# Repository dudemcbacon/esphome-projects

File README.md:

# esphome-projects
my little projects

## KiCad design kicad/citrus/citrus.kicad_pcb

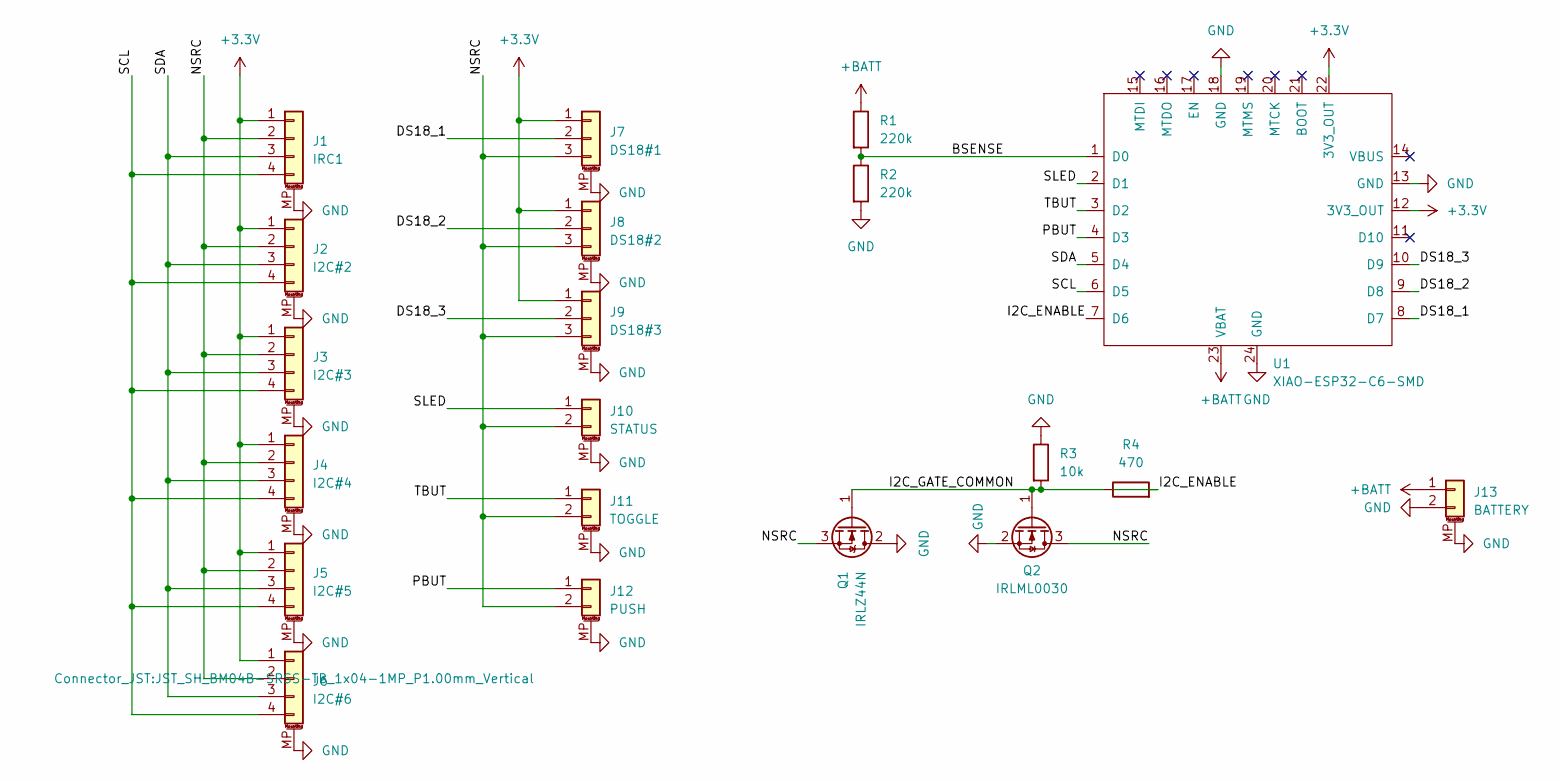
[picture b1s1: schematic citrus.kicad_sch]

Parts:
J1: IRC1; JST_SH_BM04B-SRSS-TB_1x04-1MP_P1.00mm_Vertical
J2: I2C#2; JST_SH_BM04B-SRSS-TB_1x04-1MP_P1.00mm_Vertical
J3: I2C#3; JST_SH_BM04B-SRSS-TB_1x04-1MP_P1.00mm_Vertical
J4: I2C#4; JST_SH_BM04B-SRSS-TB_1x04-1MP_P1.00mm_Vertical
J5: I2C#5; JST_SH_BM04B-SRSS-TB_1x04-1MP_P1.00mm_Vertical
J6: I2C#6; JST_SH_BM04B-SRSS-TB_1x04-1MP_P1.00mm_Vertical
J7: DS18#1; JST_SH_BM03B-SRSS-TB_1x03-1MP_P1.00mm_Vertical
J8: DS18#2; JST_SH_BM03B-SRSS-TB_1x03-1MP_P1.00mm_Vertical
J9: DS18#3; JST_SH_BM03B-SRSS-TB_1x03-1MP_P1.00mm_Vertical
J10: STATUS; JST_SH_BM02B-SRSS-TB_1x02-1MP_P1.00mm_Vertical
J11: TOGGLE; JST_SH_BM02B-SRSS-TB_1x02-1MP_P1.00mm_Vertical
J12: PUSH; JST_SH_BM02B-SRSS-TB_1x02-1MP_P1.00mm_Vertical
J13: BATTERY; JST_SH_BM02B-SRSS-TB_1x02-1MP_P1.00mm_Vertical
Q1: IRLZ44N; TO-220-3_Vertical
Q2: IRLML0030; SOT-23
R1, R2: 220k; R_Axial_DIN0207_L6.3mm_D2.5mm_P7.62mm_Horizontal
R3: 10k; R_Axial_DIN0207_L6.3mm_D2.5mm_P7.62mm_Horizontal
R4: 470; R_Axial_DIN0207_L6.3mm_D2.5mm_P7.62mm_Horizontal
U1: XIAO-ESP32-C6-SMD

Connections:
+3.3V: J1.1, J2.1, J3.1, J4.1, J5.1, J6.1, J7.1, J8.1, J9.1, U1.12 (3V3_OUT), U1.22 (3V3_OUT)
+BATT: J13.1, R1.1, U1.23 (VBAT)
/BSENSE: R1.2, R2.1, U1.1 (D0)
/DS18_1: J7.2, U1.8 (D7)
/DS18_2: J8.2, U1.9 (D8)
/DS18_3: J9.2, U1.10 (D9)
/I2C_ENABLE: R4.2, U1.7 (D6)
/I2C_GATE_COMMON: Q1.1 (G), Q2.1 (G), R3.2, R4.1
/NSRC: J1.2, J2.2, J3.2, J4.2, J5.2, J6.2, J7.3, J8.3, J9.3, J10.2, J11.2, J12.2, Q1.3 (S), Q2.3 (D)
/PBUT: J12.1, U1.4 (D3)
/SCL: J1.4, J2.4, J3.4, J4.4, J5.4, J6.4, U1.6 (D5)
/SDA: J1.3, J2.3, J3.3, J4.3, J5.3, J6.3, U1.5 (D4)
/SLED: J10.1, U1.2 (D1)
/TBUT: J11.1, U1.3 (D2)
GND: J1.MP (MountPin), J2.MP (MountPin), J3.MP (MountPin), J4.MP (MountPin), J5.MP (MountPin), J6.MP (MountPin), J7.MP (MountPin), J8.MP (MountPin), J9.MP (MountPin), J10.MP (MountPin), J11.MP (MountPin), J12.MP (MountPin), J13.2, J13.MP (MountPin), Q1.2 (D), Q2.2 (S), R2.2, R3.1, U1.13 (GND), U1.18 (GND), U1.24 (GND)

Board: 2 copper layers, 20 parts (0 on the bottom side), 15 nets, no tracks yet.

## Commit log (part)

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2026-02-26 change author
2026-03-05 add radar
2026-03-29 latest from craftroom
2026-04-15 add additional radars
2026-06-23 latest
